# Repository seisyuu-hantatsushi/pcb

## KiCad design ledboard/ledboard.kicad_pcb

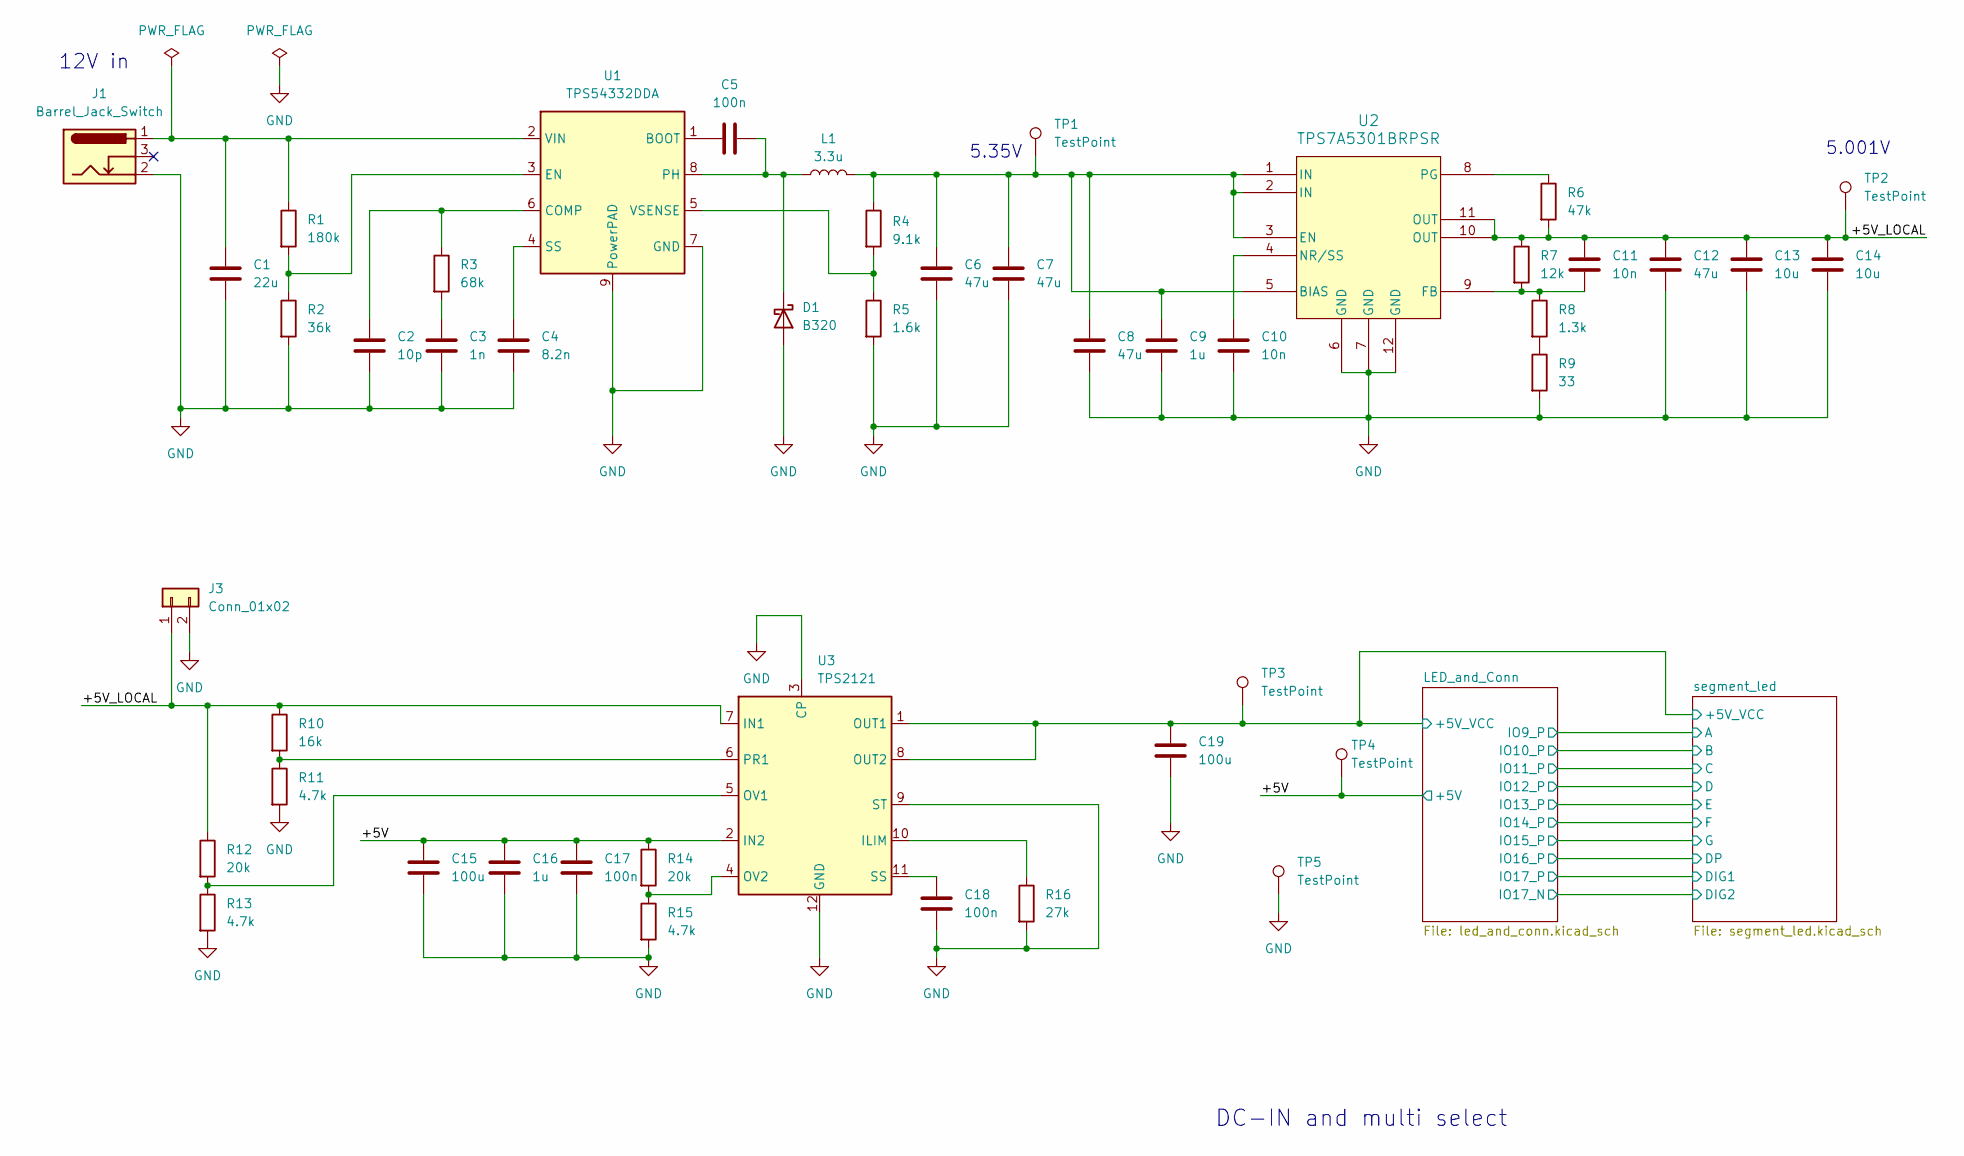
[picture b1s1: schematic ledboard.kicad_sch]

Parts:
C1: 22u; C_1206_3216Metric; MPN GRM31CC71E226ME15; LCSC Part # C5272872
C2: 10p; C_0402_1005Metric; MPN GRM1555C1E100JA01D; LCSC Part # C161512
C3: 1n; C_0201_0603Metric; MPN GRM033R71C102KA01; LCSC Part # C76942
C4: 8.2n; C_0201_0603Metric; MPN GRM033R61E822KA12D; LCSC Part # C710826
C5, C17, C18: 100n; C_0201_0603Metric; MPN GRM033C81E104ME14; LCSC Part # C412246
C6, C7, C8, C12: 47u; C_1206_3216Metric; MPN GRM31CR61C476ME44; LCSC Part # C385047
C9, C16: 1u; C_0402_1005Metric; MPN GRM155C81A105KA12D; LCSC Part # C162161
C10, C11: 10n; C_0402_1005Metric; MPN GRM155R71C103KA01D; LCSC Part # C85735
C13, C14: 10u; C_0603_1608Metric; MPN GRM188C81C106MA73D; LCSC Part # C182375
C15, C19: 100u; C_1210_3225Metric; MPN GRM32ER61A107ME20; LCSC Part # C84455
D1: B320; D_SMC; MPN B320-13-F; LCSC Part # C134448
J1: Barrel_Jack_Switch; MPD_EJ503A; MPN EJ503A; LCSC Part # C3095117
J3: Conn_01x02; PinHeader_1x02_P2.54mm_Vertical
L1: 3.3u; IND_BOURNS_SRN8040; MPN SRN8040-3R3Y; LCSC Part # C780188
R1: 180k; R_0603_1608Metric; MPN RC0603FR-07180KL; LCSC Part # C123419
R2: 36k; R_0603_1608Metric; MPN RC0603FR-0736KL; LCSC Part # C114619
R3: 68k; R_0603_1608Metric; MPN RC0603FR-0768KL; LCSC Part # C114633
R4: 9.1k; R_0603_1608Metric; MPN RC0603FR-0769K1L; LCSC Part # C114639
R5: 1.6k; R_0603_1608Metric; MPN RC0603FR-071K6L; LCSC Part # C165489
R6: 47k; R_0603_1608Metric; MPN RC0603FR-0747KL; LCSC Part # C105579
R7: 12k; R_0603_1608Metric; MPN RC0603FR-0712KL; LCSC Part # C114659
R8: 1.3k; R_0603_1608Metric; MPN RC0603FR-071K3L; LCSC Part # C125319
R9: 33; R_0603_1608Metric; MPN RC0603FR-0733RL; LCSC Part # C108661
R10: 16k; R_0603_1608Metric; MPN RC0603FR-0716KL; LCSC Part # C137788
R11, R13, R15: 4.7k; R_0603_1608Metric; MPN RC0603FR-074K7L; LCSC Part # C99782
R12, R14: 20k; R_0603_1608Metric; MPN RC0603FR-0720KL; LCSC Part # C105575
R16: 27k; R_0603_1608Metric; MPN RC0603FR-0727KL; LCSC Part # C114614
TP1, TP2, TP3, TP4, TP5: TestPoint; TestPoint_Keystone_5000-5004_Miniature; MPN 5002; LCSC Part # C238123
U1: TPS54332DDA; DDA8_3X2P13; MPN TPS54332DDAR; LCSC Part # C41312
U2: TPS7A5301BRPSR; VQFN-HR12_RPS_TEX; MPN TPS7A5301BRPSR; LCSC Part # C2868223
U3: TPS2121; RUX0012A; MPN TPS2121RUXR; LCSC Part # C485916

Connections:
/+5V: C15.1, C16.1, C17.1, R14.1, TP4.1, U3.2 (IN2); also elsewhere on the board
/+5V_LOCAL: C11.1, C12.1, C13.1, C14.1, J3.1, R6.2, R7.1, R10.1, R12.1, TP2.1, U2.10 (OUT), U2.11 (OUT), U3.7 (IN1)
/LED_and_Conn/+5V_VCC: C19.1, TP3.1, U3.1 (OUT1), U3.8 (OUT2); also elsewhere on the board
GND: C1.2, C2.2, C3.2, C4.2, C6.2, C7.2, C8.2, C9.2, C10.2, C12.2, C13.2, C14.2, C15.2, C16.2, C17.2, C18.2, C19.2, D1.2 (A), J1.2, J3.2, R2.2, R5.2, R9.2, R11.2, R13.2, R15.2, R16.2, TP5.1, U1.7 (GND), U1.9 (PowerPAD), U2.6 (GND), U2.7 (GND), U2.12 (GND), U3.3 (CP), U3.9 (ST), U3.12 (GND); also elsewhere on the board
unnamed: C3.1, R3.2
unnamed: C5.1, D1.1 (K), L1.1, U1.8 (PH)
unnamed: R8.2, R9.1
unnamed: C5.2, U1.1 (BOOT)
unnamed: C2.1, R3.1, U1.6 (COMP)
unnamed: R1.2, R2.1, U1.3 (EN)
unnamed: C4.1, U1.4 (SS)
unnamed: C1.1, J1.1, R1.1, U1.2 (VIN)
unnamed: R4.2, R5.1, U1.5 (VSENSE)
unnamed: C6.1, C7.1, C8.1, C9.1, L1.2, R4.1, TP1.1, U2.1 (IN), U2.2 (IN), U2.3 (EN), U2.5 (BIAS)
unnamed: C11.2, R7.2, R8.1, U2.9 (FB)
unnamed: C10.1, U2.4 (NR/SS)
unnamed: R6.1, U2.8 (PG)
unnamed: R16.1, U3.10 (ILIM)
unnamed: R12.2, R13.1, U3.5 (OV1)
unnamed: R14.2, R15.1, U3.4 (OV2)
unnamed: R10.2, R11.1, U3.6 (PR1)
unnamed: C18.1, U3.11 (SS)

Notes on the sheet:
12V in
DC-IN and multi select
5.001V
5.35V

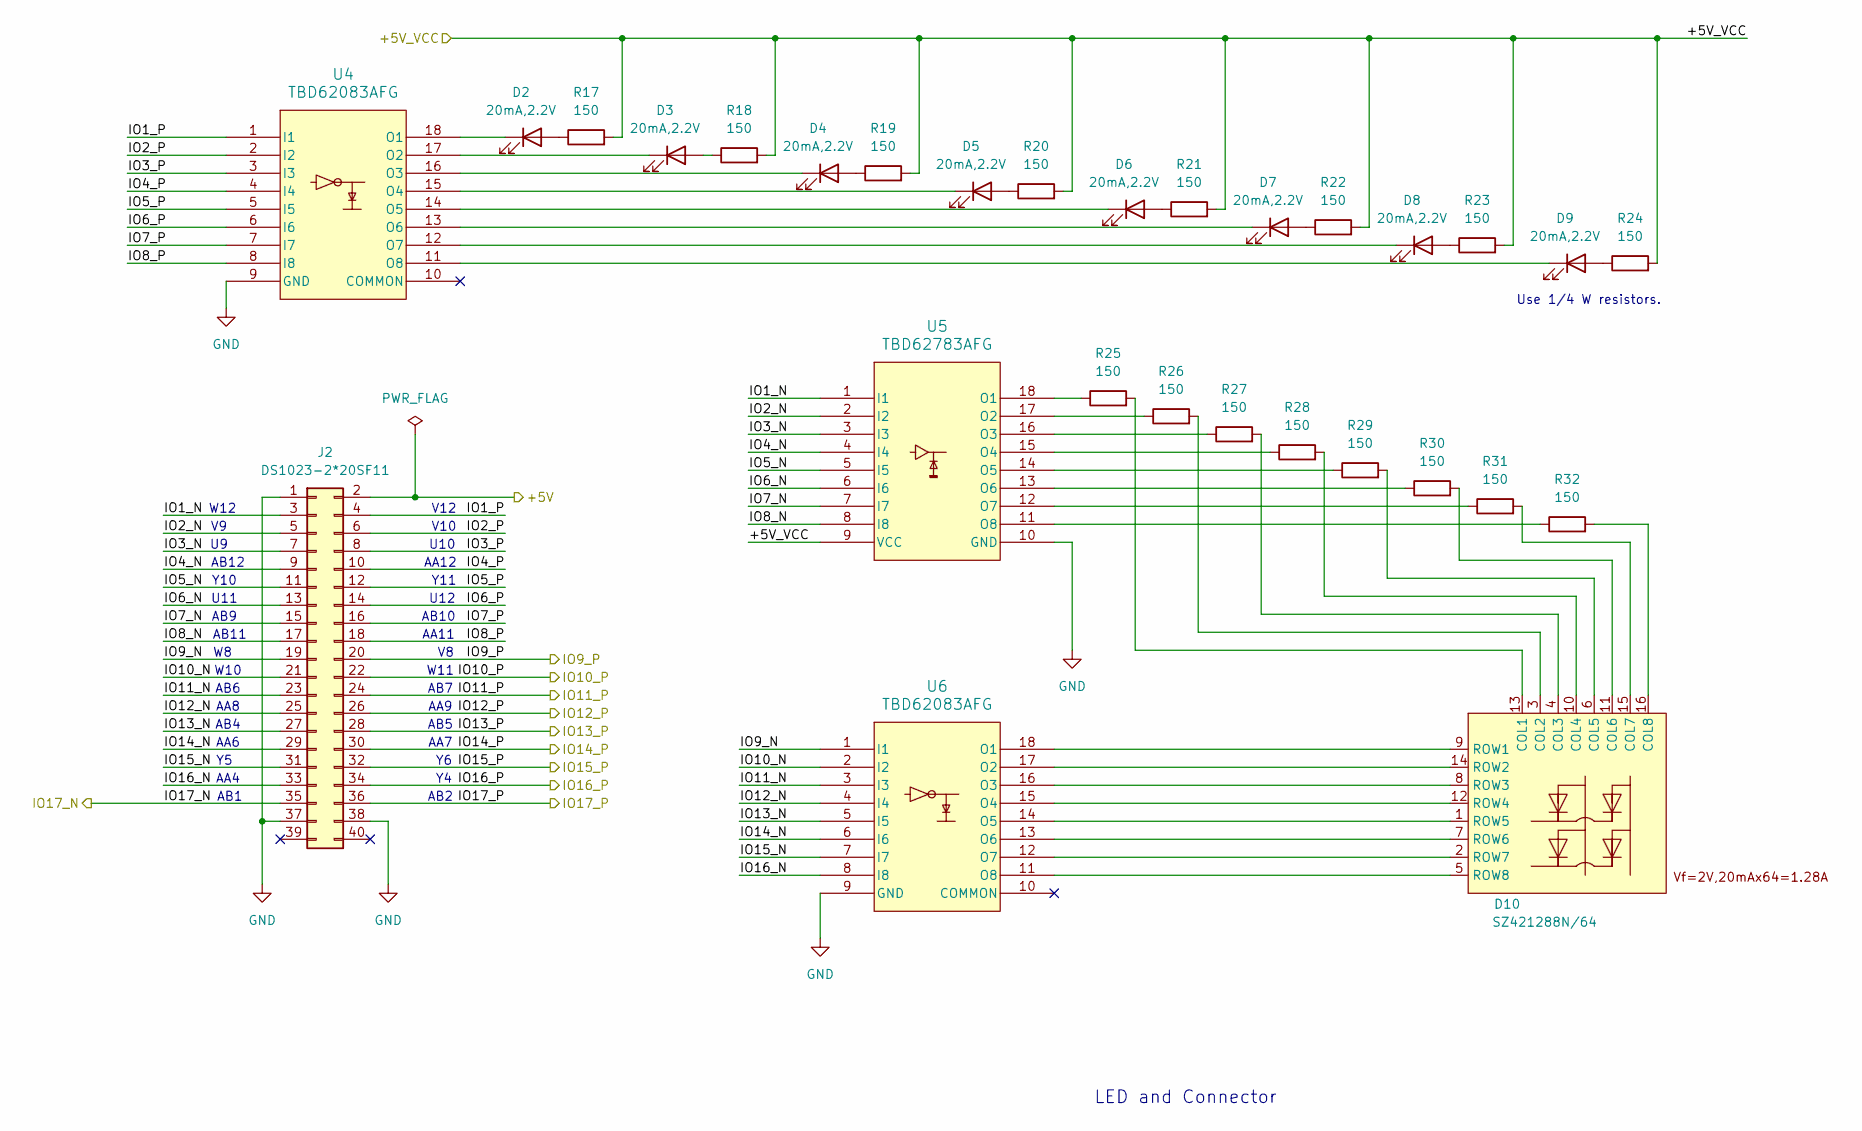
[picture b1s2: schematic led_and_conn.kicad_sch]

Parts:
D2, D3, D4, D5, D6, D7, D8, D9: 20mA,2.2V; LED_0603_1608Metric; MPN SML-D12V8WT86C; LCSC Part # C458032
D10: SZ421288N/64; SZ421288N_64; MPN SZ421288N/64; LCSC Part # C2980922
J2: DS1023-2*20SF11; PinSocket_2x20_P2.54mm_Vertical; MPN DS1023-2*20SF11; LCSC Part # C132132
R17, R18, R19, R20, R21, R22, R23, R24, R25, R26, R27, R28, R29, R30, R31, R32: 150; R_0603_1608Metric; MPN SR0603FR-7T150RL; LCSC Part # C873675
U4, U6: TBD62083AFG; SOP18-P-375-1p27_TOS; MPN TBD62083AFG; LCSC Part # C163228
U5: TBD62783AFG; SOP18-P-375-1p27_TOS; MPN TBD62783AFG; LCSC Part # C97745

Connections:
/+5V: J2.2; also elsewhere on the board
/LED_and_Conn/+5V_VCC: R17.2, R18.2, R19.2, R20.2, R21.2, R22.2, R23.2, R24.2, U5.9 (VCC); also elsewhere on the board
/LED_and_Conn/IO1_N: J2.3, U5.1 (I1)
/LED_and_Conn/IO1_P: J2.4, U4.1 (I1)
/LED_and_Conn/IO2_N: J2.5, U5.2 (I2)
/LED_and_Conn/IO2_P: J2.6, U4.2 (I2)
/LED_and_Conn/IO3_N: J2.7, U5.3 (I3)
/LED_and_Conn/IO3_P: J2.8, U4.3 (I3)
/LED_and_Conn/IO4_N: J2.9, U5.4 (I4)
/LED_and_Conn/IO4_P: J2.10, U4.4 (I4)
/LED_and_Conn/IO5_N: J2.11, U5.5 (I5)
/LED_and_Conn/IO5_P: J2.12, U4.5 (I5)
/LED_and_Conn/IO6_N: J2.13, U5.6 (I6)
/LED_and_Conn/IO6_P: J2.14, U4.6 (I6)
/LED_and_Conn/IO7_N: J2.15, U5.7 (I7)
/LED_and_Conn/IO7_P: J2.16, U4.7 (I7)
/LED_and_Conn/IO8_N: J2.17, U5.8 (I8)
/LED_and_Conn/IO8_P: J2.18, U4.8 (I8)
/LED_and_Conn/IO9_N: J2.19, U6.1 (I1)
/LED_and_Conn/IO9_P: J2.20; also elsewhere on the board
/LED_and_Conn/IO10_N: J2.21, U6.2 (I2)
/LED_and_Conn/IO10_P: J2.22; also elsewhere on the board
/LED_and_Conn/IO11_N: J2.23, U6.3 (I3)
/LED_and_Conn/IO11_P: J2.24; also elsewhere on the board
/LED_and_Conn/IO12_N: J2.25, U6.4 (I4)
/LED_and_Conn/IO12_P: J2.26; also elsewhere on the board
/LED_and_Conn/IO13_N: J2.27, U6.5 (I5)
/LED_and_Conn/IO13_P: J2.28; also elsewhere on the board
/LED_and_Conn/IO14_N: J2.29, U6.6 (I6)
/LED_and_Conn/IO14_P: J2.30; also elsewhere on the board
/LED_and_Conn/IO15_N: J2.31, U6.7 (I7)
/LED_and_Conn/IO15_P: J2.32; also elsewhere on the board
/LED_and_Conn/IO16_N: J2.33, U6.8 (I8)
/LED_and_Conn/IO16_P: J2.34; also elsewhere on the board
/LED_and_Conn/IO17_N: J2.35; also elsewhere on the board
/LED_and_Conn/IO17_P: J2.36; also elsewhere on the board
GND: J2.1, J2.37, J2.38, U4.9 (GND), U5.10 (GND), U6.9 (GND); also elsewhere on the board
unnamed: D2.2 (A), R17.1
unnamed: D2.1 (K), U4.18 (O1)
unnamed: D3.2 (A), R18.1
unnamed: D3.1 (K), U4.17 (O2)
unnamed: D4.2 (A), R19.1
unnamed: D4.1 (K), U4.16 (O3)
unnamed: D5.2 (A), R20.1
unnamed: D5.1 (K), U4.15 (O4)
unnamed: D6.2 (A), R21.1
unnamed: D6.1 (K), U4.14 (O5)
unnamed: D7.2 (A), R22.1
unnamed: D7.1 (K), U4.13 (O6)
unnamed: D8.2 (A), R23.1
unnamed: D8.1 (K), U4.12 (O7)
unnamed: D9.2 (A), R24.1
unnamed: D9.1 (K), U4.11 (O8)
unnamed: D10.13 (COL1), R25.2
unnamed: D10.3 (COL2), R26.2
unnamed: D10.4 (COL3), R27.2
unnamed: D10.10 (COL4), R28.2
unnamed: D10.6 (COL5), R29.2
unnamed: D10.11 (COL6), R30.2
unnamed: D10.15 (COL7), R31.2
unnamed: D10.16 (COL8), R32.2
unnamed: D10.9 (ROW1), U6.18 (O1)
unnamed: D10.14 (ROW2), U6.17 (O2)
unnamed: D10.8 (ROW3), U6.16 (O3)
unnamed: D10.12 (ROW4), U6.15 (O4)
unnamed: D10.1 (ROW5), U6.14 (O5)
unnamed: D10.7 (ROW6), U6.13 (O6)
unnamed: D10.2 (ROW7), U6.12 (O7)
unnamed: D10.5 (ROW8), U6.11 (O8)
unnamed: R25.1, U5.18 (O1)
unnamed: R26.1, U5.17 (O2)
unnamed: R27.1, U5.16 (O3)
unnamed: R28.1, U5.15 (O4)
unnamed: R29.1, U5.14 (O5)
unnamed: R30.1, U5.13 (O6)
unnamed: R31.1, U5.12 (O7)
unnamed: R32.1, U5.11 (O8)

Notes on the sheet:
U12
AA12
W11
U10
AB4
AB1
AA8
AB2
AB5
Y11
AA4
Y10
AB10
AA9
V10
AB6
W12
LED and Connector
AB7
Use 1/4 W resistors.
AB9
AA6
V12
U11
AA7
AB11
AA11
AB12
W10

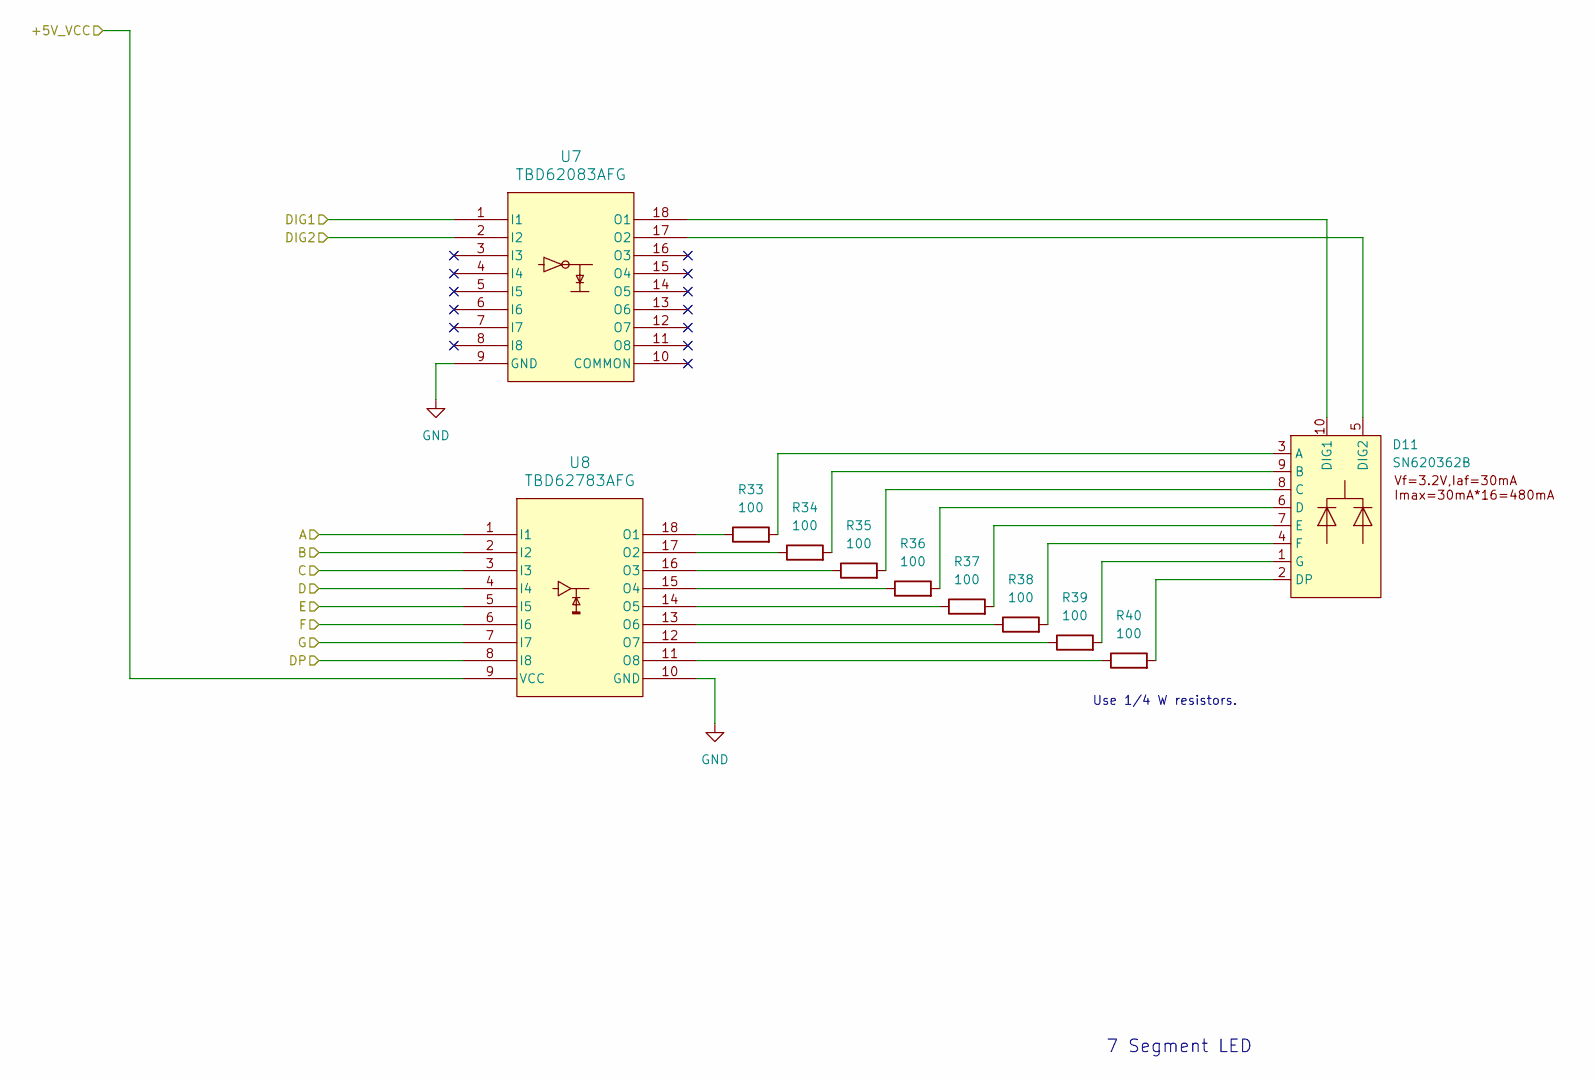
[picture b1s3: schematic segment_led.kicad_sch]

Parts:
D11: SN620362B; MPN SN620362B; LCSC Part # C96556
R33, R34, R35, R36, R37, R38, R39, R40: 100; R_0603_1608Metric; MPN SR0603FR-7T100RL; LCSC Part # C873671
U7: TBD62083AFG; SOP18-P-375-1p27_TOS; MPN TBD62083AFG; LCSC Part # C163228
U8: TBD62783AFG; SOP18-P-375-1p27_TOS; MPN TBD62783AFG; LCSC Part # C97745

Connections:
/LED_and_Conn/+5V_VCC: U8.9 (VCC); also elsewhere on the board
/LED_and_Conn/IO9_P: U8.1 (I1); also elsewhere on the board
/LED_and_Conn/IO10_P: U8.2 (I2); also elsewhere on the board
/LED_and_Conn/IO11_P: U8.3 (I3); also elsewhere on the board
/LED_and_Conn/IO12_P: U8.4 (I4); also elsewhere on the board
/LED_and_Conn/IO13_P: U8.5 (I5); also elsewhere on the board
/LED_and_Conn/IO14_P: U8.6 (I6); also elsewhere on the board
/LED_and_Conn/IO15_P: U8.7 (I7); also elsewhere on the board
/LED_and_Conn/IO16_P: U8.8 (I8); also elsewhere on the board
/LED_and_Conn/IO17_N: U7.2 (I2); also elsewhere on the board
/LED_and_Conn/IO17_P: U7.1 (I1); also elsewhere on the board
GND: U7.9 (GND), U8.10 (GND); also elsewhere on the board
unnamed: D11.3 (A), R33.2
unnamed: D11.9 (B), R34.2
unnamed: D11.8 (C), R35.2
unnamed: D11.6 (D), R36.2
unnamed: D11.10 (DIG1), U7.18 (O1)
unnamed: D11.5 (DIG2), U7.17 (O2)
unnamed: D11.2 (DP), R40.2
unnamed: D11.7 (E), R37.2
unnamed: D11.4 (F), R38.2
unnamed: D11.1 (G), R39.2
unnamed: R33.1, U8.18 (O1)
unnamed: R34.1, U8.17 (O2)
unnamed: R35.1, U8.16 (O3)
unnamed: R36.1, U8.15 (O4)
unnamed: R37.1, U8.14 (O5)
unnamed: R38.1, U8.13 (O6)
unnamed: R39.1, U8.12 (O7)
unnamed: R40.1, U8.11 (O8)

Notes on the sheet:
7 Segment LED
Use 1/4 W resistors.

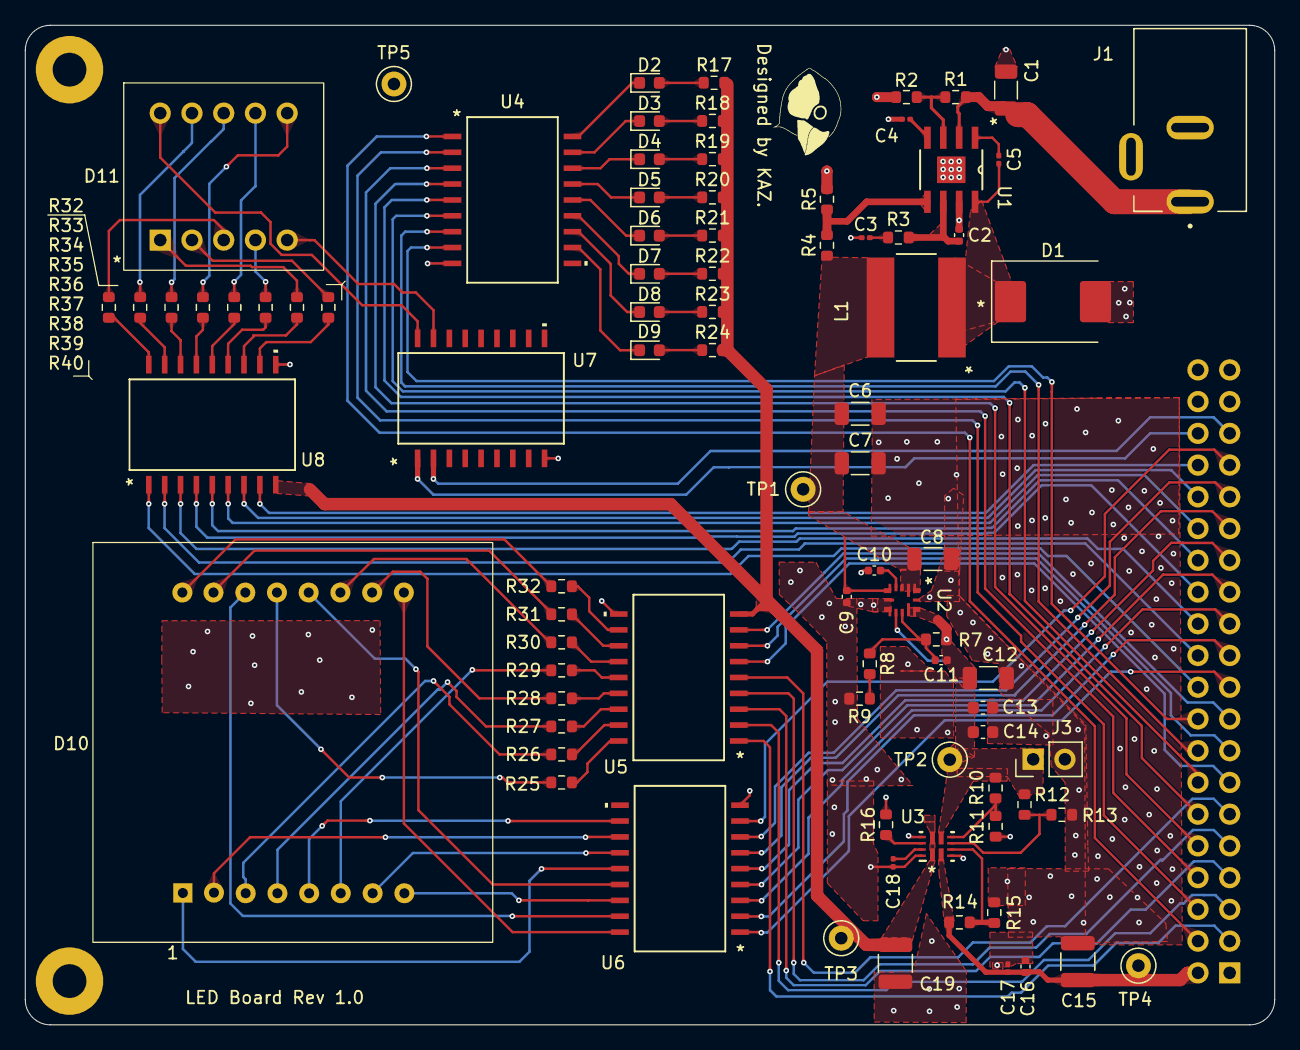
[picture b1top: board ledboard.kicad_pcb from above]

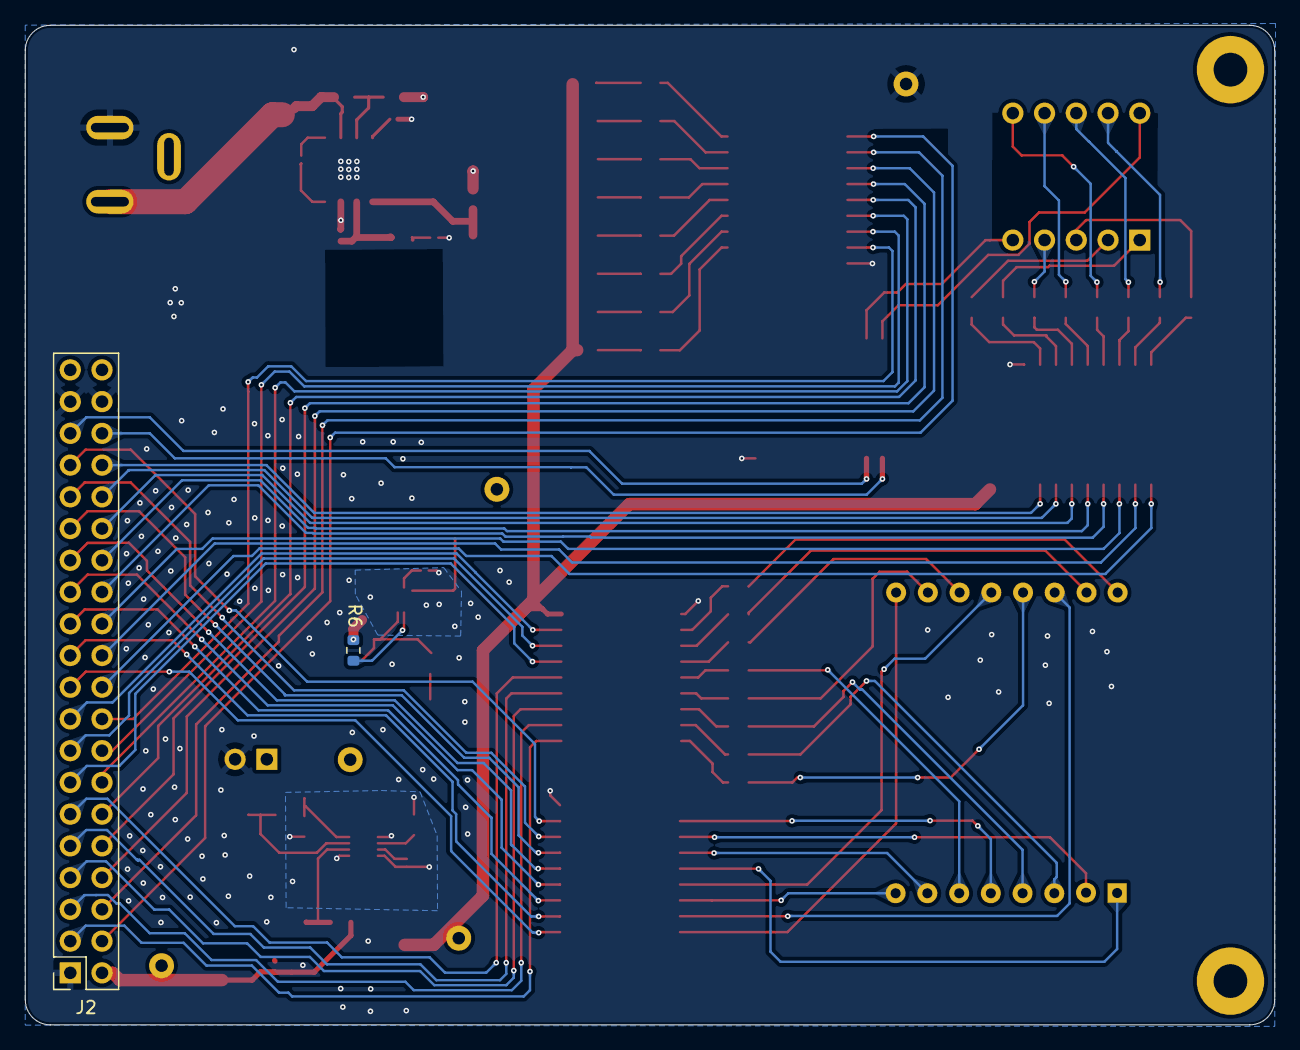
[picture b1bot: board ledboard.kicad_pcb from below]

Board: 2 copper layers, 100.0 x 80.0 mm, 87 parts (2 on the bottom side), 114 nets.

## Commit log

2026-03-28 Temporary schematic fix.
2026-03-29 各種定数見直し,TPS2121の前後にデカップリングコンデンサを配置.
2026-03-29 部品の再アノテーションを行う.
2026-04-04 部品が決まったので,コミットします.
2026-04-04 ERC解消まで.
2026-04-05 PCB1レイアウトを開始.
2026-04-12 PCBデザイン. 未結線がなくなったところまで.
2026-04-12 アートワーク完了.
2026-04-13 log用のフットプリント追加.
2026-04-13 LOGとボード名を追加します.
2026-04-14 部品変更とアートワークの修正.
2026-04-16 LSCS品番を追加. コンデンサの品番を変更します.
2026-04-18 L1をBOURNS SR8040-3R3Yに変更しました.
